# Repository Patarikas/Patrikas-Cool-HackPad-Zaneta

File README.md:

# Patrikas's-Cool-HackPad-Žaneta
My HackPad is called Žaneta. It has 6 keys, a rotary encoder and an OLED display.

## What does it do
The keys are for shortcuts in edditing softwares and 3D modeling softwares also they will be used as switches for lights, turn signals and other car features in games like BeamNG Drive and RFactor.

The Rotary encoder will be used for adjusting the volume

And the Display will show the volume. I plan on adding more features to the display but this is all for now.

## The Case
The case has 3 pieces: the main body, the top cover and the bottom piece whitch seeds the XIAO and inclines the whole HackPad for better use.

It fits together using 7 M3 bolts and 7 heatset inserts, 1 for the PCB, 2 for attaching the bottom piece and 4 for the top cover.

(The case is just from the default material and the keycaps are not plain because in the 3D models I downloaded weren't any plain ones, and even creating this case took me too much time and energy, so I just left it how it is.)

## The PCB and the Schematics
I made it all in KiCad and the PCB has a silk screen with the name of the HackPad.

## The Firmware
So I made my firmware using VSC and it's chat function, because I just can't wrap  my head around code in general, and even creating the PCB and using Fusion for the first time was a little too much for me. But I plan on learning basic coding in the near future.

## BOM
- 6x MX Switches
- 6x Keycaps
- 7x M3x5x4 Heatset inserts
- 7x M3x6 Bolts
- 3D printed Case parts

## Some Extra Words 
This project was realy fun but really hard and frustrating at the same time. The reason for that is that working in new to me programs and learning how to do stuff in them was really time consuming, preticulary Fusion because previously I've worked in other 3D modeling softwares and Fusion is really different from all of them.
The last thing that I want to say is thanks to all of the people that took part in this, because I wanted to learn how to make something like this for a long time, but I didn't know where to begin.
(Also I am sorry for any miss spelled or badly used words, because English is not my first language)

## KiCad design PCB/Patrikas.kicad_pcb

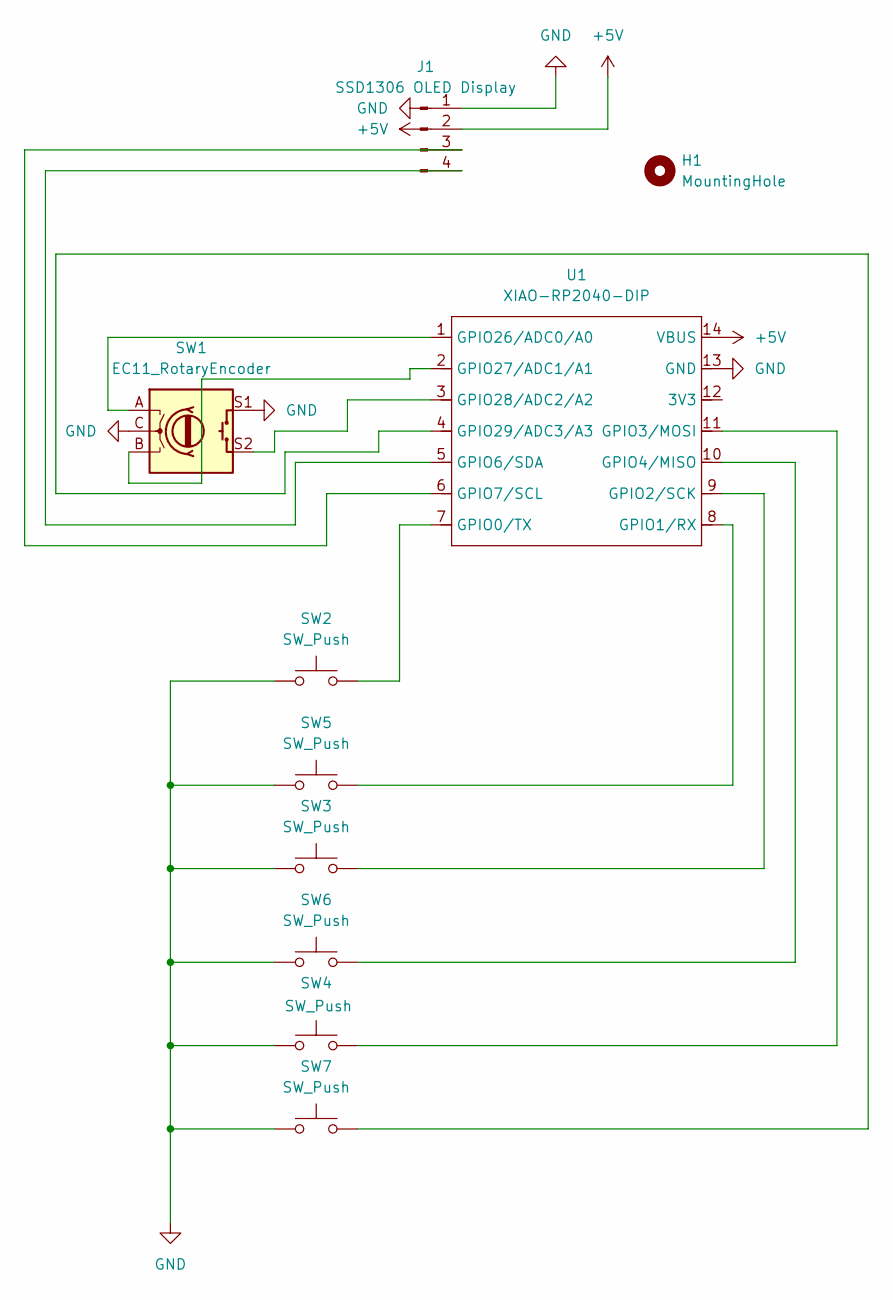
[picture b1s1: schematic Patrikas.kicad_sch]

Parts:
H1: MountingHole; MountingHole_3.2mm_M3
J1: SSD1306 OLED Display; 128x64OLED
SW1: EC11_RotaryEncoder; RotaryEncoder_Alps_EC11E-Switch_Vertical_H20mm
SW2, SW3, SW4, SW5, SW6, SW7: SW_Push; SW_Cherry_MX_1.00u_PCB
U1: XIAO-RP2040-DIP

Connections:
+5V: J1.2, U1.14 (VBUS)
GND: J1.1, SW1.C, SW1.S1, SW2.1, SW3.1, SW4.1, SW5.1, SW6.1, SW7.1, U1.13 (GND)
unnamed: J1.3, U1.6 (GPIO7/SCL)
unnamed: J1.4, U1.5 (GPIO6/SDA)
unnamed: SW2.2, U1.7 (GPIO0/TX)
unnamed: SW5.2, U1.8 (GPIO1/RX)
unnamed: SW3.2, U1.9 (GPIO2/SCK)
unnamed: SW4.2, U1.11 (GPIO3/MOSI)
unnamed: SW6.2, U1.10 (GPIO4/MISO)
unnamed: SW1.A, U1.1 (GPIO26/ADC0/A0)
unnamed: SW1.B, U1.2 (GPIO27/ADC1/A1)
unnamed: SW1.S2, U1.3 (GPIO28/ADC2/A2)
unnamed: SW7.2, U1.4 (GPIO29/ADC3/A3)

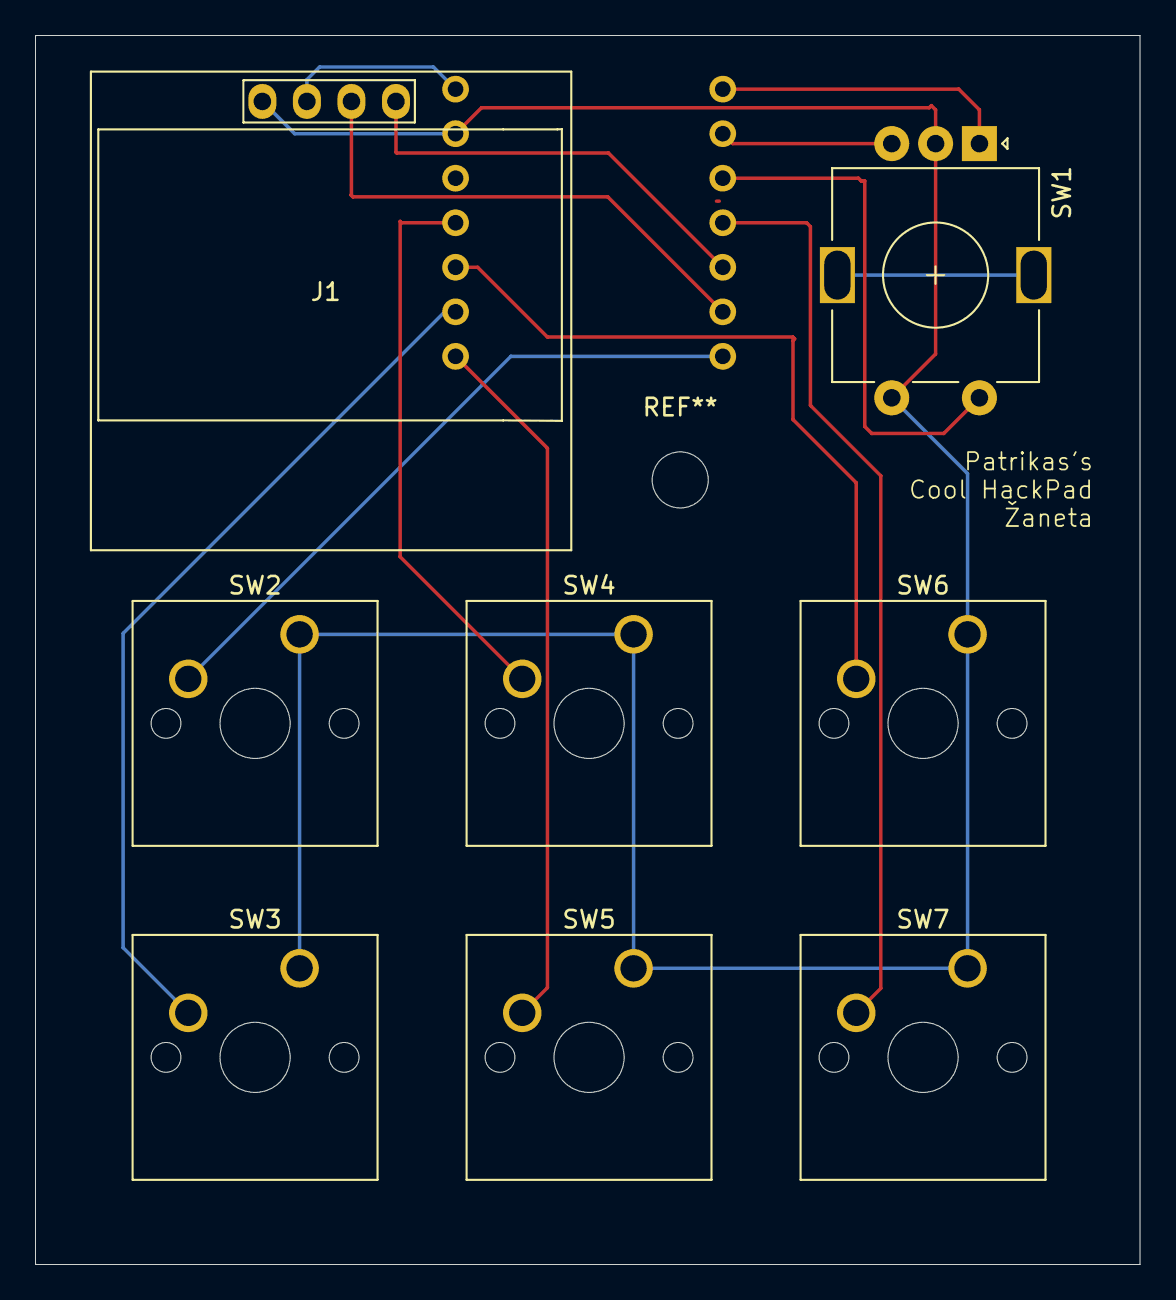
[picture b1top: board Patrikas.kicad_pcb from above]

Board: 2 copper layers, 63.0 x 70.1 mm, 9 parts (1 on the bottom side), 13 nets.

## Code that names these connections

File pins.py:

# Pin configuration for Seeed XIAO RP2040
# Pins are based on XIAO RP2040 pinout

# MX-Style Switch pins
SWITCH_PINS = {
    'switch_1': 0,   # GPIO0 - D0
    'switch_2': 1,   # GPIO1 - D1
    'switch_3': 2,   # GPIO2 - D2
    'switch_4': 3,   # GPIO3 - D3
    'switch_5': 4,   # GPIO4 - D4
    'switch_6': 5,   # GPIO5 - D5
}

# EC11 Rotary Encoder pins
ENCODER_CLK = 28    # GPIO28 - D8 (Clock signal)
ENCODER_DT = 27     # GPIO27 - D7 (Data signal)
ENCODER_SW = 26     # GPIO26 - D6 (Switch/Button)

# OLED Display pins (SSD1306 - I2C)
OLED_SDA = 6        # GPIO6 - D4 (I2C SDA)
OLED_SCL = 7        # GPIO7 - D5 (I2C SCL)
OLED_I2C_ID = 0     # I2C bus 0
OLED_I2C_FREQ = 400000  # 400kHz

# Display settings
OLED_WIDTH = 128
OLED_HEIGHT = 64
OLED_ADDR = 0x3C    # I2C address for SSD1306

# Debounce time in milliseconds
DEBOUNCE_TIME = 20

# Encoder settings
ENCODER_DEBOUNCE_TIME = 2  # ms for encoder contacts

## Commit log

2026-01-21 Enhance README with project details and personal insights
    Added detailed project description, including features, case design, PCB schematics, firmware information, BOM, and personal reflections.
2026-01-21 Add README for Žaneta HackPad project
    Added detailed project description for Žaneta HackPad, including features, case design, PCB schematics, firmware development, and BOM.
2026-01-21 added folders with models and code
